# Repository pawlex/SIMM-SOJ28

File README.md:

# SIMM-SOJ28
Another 30 pin SIMM module based on whatever FP ASYNC DRAM I could find new old stock at the time.
## Design Goals
+ 2 layer
+ Low cost
+ Flexible decoupling
+ Minimal BOM

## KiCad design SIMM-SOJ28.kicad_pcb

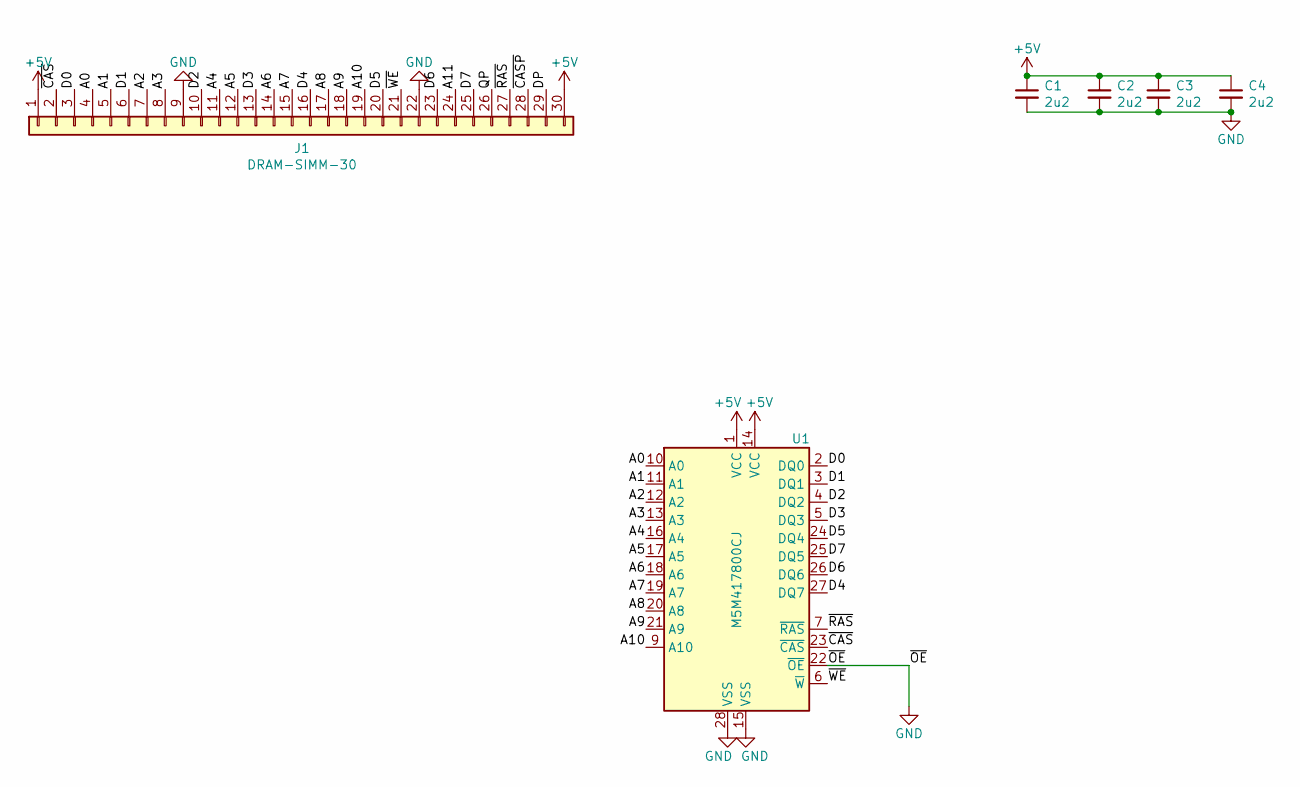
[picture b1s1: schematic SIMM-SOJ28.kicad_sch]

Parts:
C1, C2, C3, C4: 2u2; C_0805_2012Metric_Pad1.18x1.45mm_HandSolder
J1: DRAM-SIMM-30; SIMM-30_Edge
U1: M5M417800CJ; SOJ-28_10.16x18.415mm_P1.27mm

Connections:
+5V: C1.1, C2.1, C3.1, C4.1, J1.1, J1.30, U1.1 (VCC), U1.14 (VCC)
/A0: J1.4, U1.10 (A0)
/A1: J1.5, U1.11 (A1)
/A2: J1.7, U1.12 (A2)
/A3: J1.8, U1.13 (A3)
/A4: J1.11, U1.16 (A4)
/A5: J1.12, U1.17 (A5)
/A6: J1.14, U1.18 (A6)
/A7: J1.15, U1.19 (A7)
/A8: J1.17, U1.20 (A8)
/A9: J1.18, U1.21 (A9)
/A10: J1.19, U1.9 (A10)
/A11: J1.24
/D0: J1.3, U1.2 (DQ0)
/D1: J1.6, U1.3 (DQ1)
/D2: J1.10, U1.4 (DQ2)
/D3: J1.13, U1.5 (DQ3)
/D4: J1.16, U1.27 (DQ7)
/D5: J1.20, U1.24 (DQ4)
/D6: J1.23, U1.26 (DQ6)
/D7: J1.25, U1.25 (DQ5)
/DP: J1.29
/QP: J1.26
/~CASP: J1.28
/~CAS: J1.2, U1.23 (~CAS)
/~RAS: J1.27, U1.7 (~RAS)
/~WE: J1.21, U1.6 (~W)
GND: C1.2, C2.2, C3.2, C4.2, J1.9, J1.22, U1.15 (VSS), U1.22 (~OE), U1.28 (VSS)

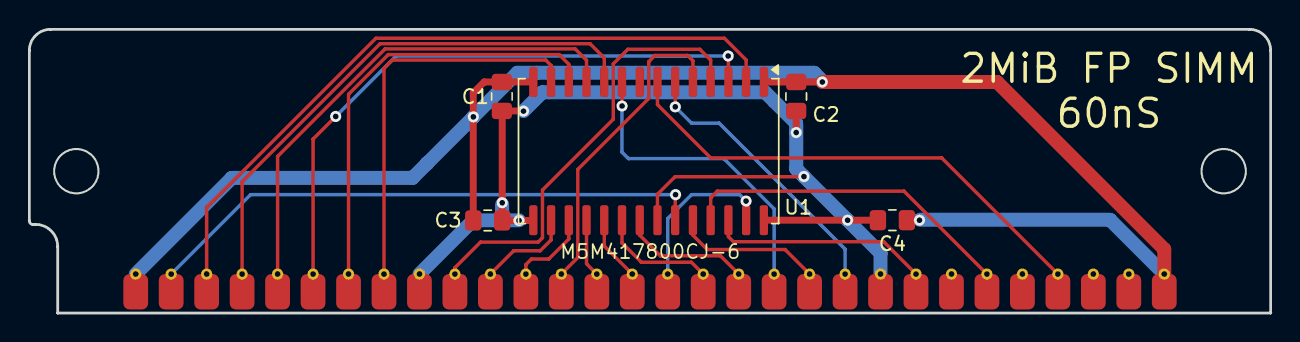
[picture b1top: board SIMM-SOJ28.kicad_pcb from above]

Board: 2 copper layers, 88.9 x 20.3 mm, 6 parts (0 on the bottom side), 24 nets.

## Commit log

2025-11-10 Version 1.0 Commit
2025-11-10 remove old naming conventions
2025-11-10 cleaning up repo
2025-11-10 Update README.md
    Added simple Screenshot
